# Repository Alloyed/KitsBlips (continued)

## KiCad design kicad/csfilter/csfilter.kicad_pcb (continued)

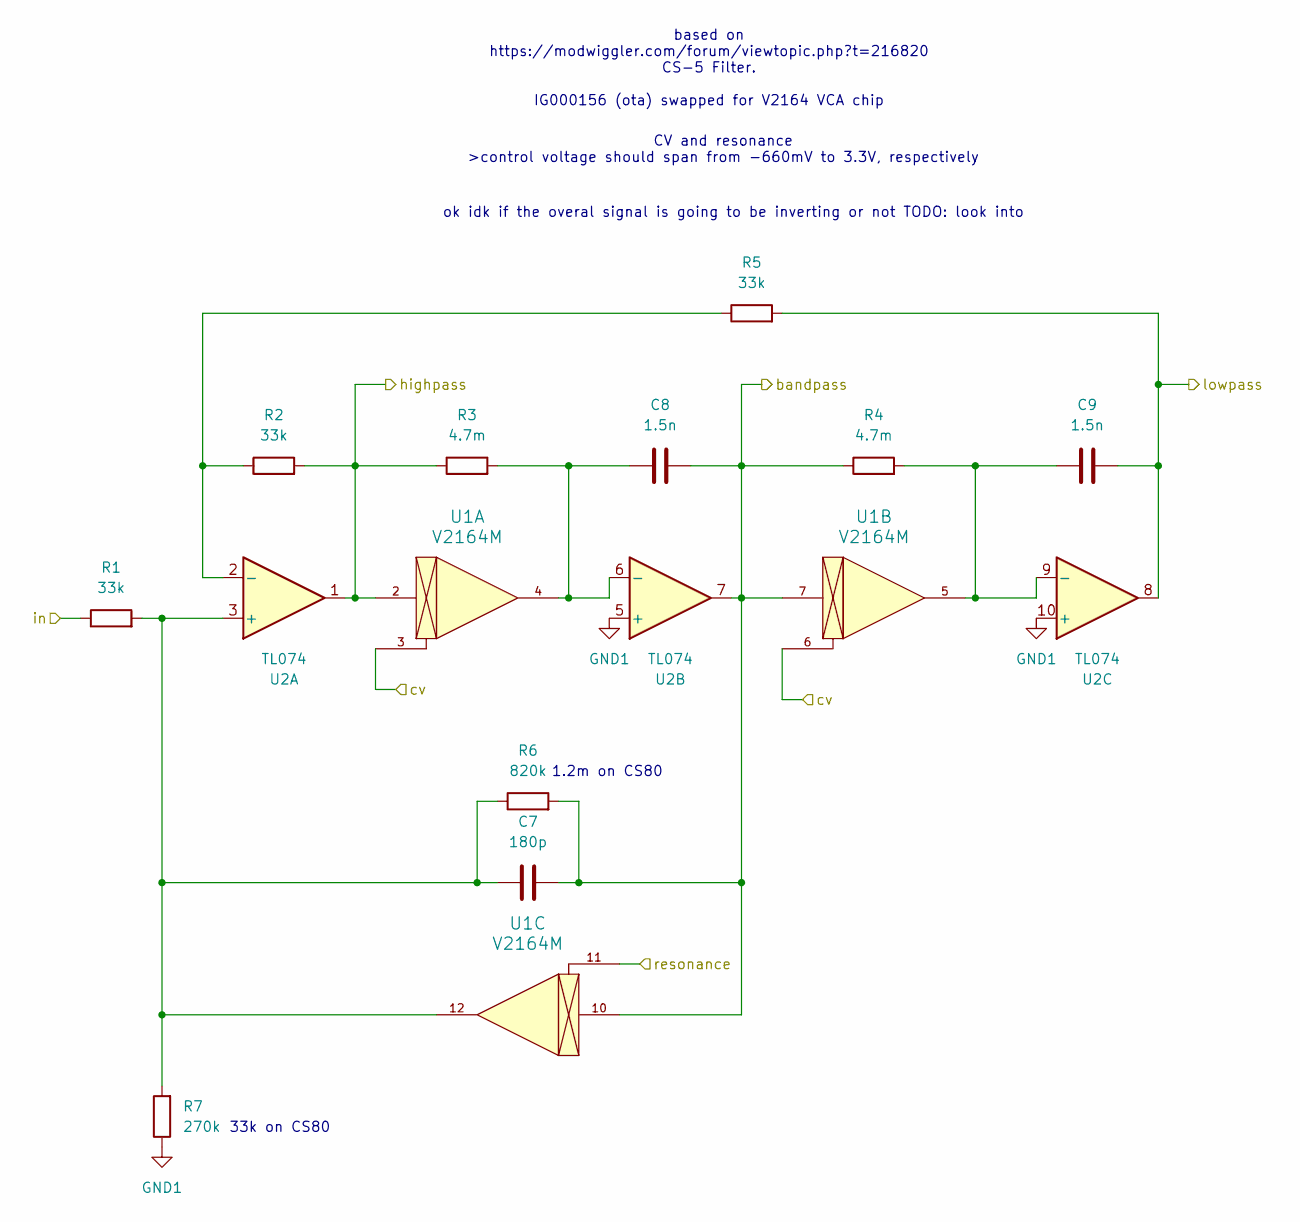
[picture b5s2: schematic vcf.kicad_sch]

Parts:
C7: 180p; C_Disc_D6.0mm_W2.5mm_P5.00mm
C8, C9: 1.5n; C_Disc_D6.0mm_W2.5mm_P5.00mm
R1, R2, R5: 33k; R_Axial_DIN0207_L6.3mm_D2.5mm_P7.62mm_Horizontal
R3, R4: 4.7m; R_Axial_DIN0207_L6.3mm_D2.5mm_P7.62mm_Horizontal
R6: 820k; R_Axial_DIN0207_L6.3mm_D2.5mm_P7.62mm_Horizontal
R7: 270k; R_Axial_DIN0207_L6.3mm_D2.5mm_P7.62mm_Horizontal
U1: V2164M; DIP-16_W7.62mm_Socket
U2: TL074; DIP-14_W7.62mm_Socket

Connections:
/input-cv1/A_OUT: U1.11; also elsewhere on the board
/input-cv/A_OUT: U1.3, U1.6; also elsewhere on the board
/vcf/bandpass: C7.2, C8.2, R4.1, R6.2, U1.7, U1.10, U2.7; also elsewhere on the board
/vcf/in: R1.1; also elsewhere on the board
/vcf/lowpass: C9.2, R5.2, U2.8; also elsewhere on the board
GND1: R7.1, U2.5 (+), U2.10 (+); also elsewhere on the board
unnamed: C7.1, R1.2, R6.1, R7.2, U1.12, U2.3 (+)
unnamed: C8.1, R3.2, U1.4, U2.6 (-)
unnamed: C9.1, R4.2, U1.5, U2.9 (-)

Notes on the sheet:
CV and resonance >control voltage should span from -660mV to 3.3V, respectively
33k on CS80
based on https://modwiggler.com/forum/viewtopic.php?t=216820 CS-5 Filter. IG000156 (ota) swapped for V2164 VCA chip
1.2m on CS80
ok idk if the overal signal is going to be inverting or not TODO: look into

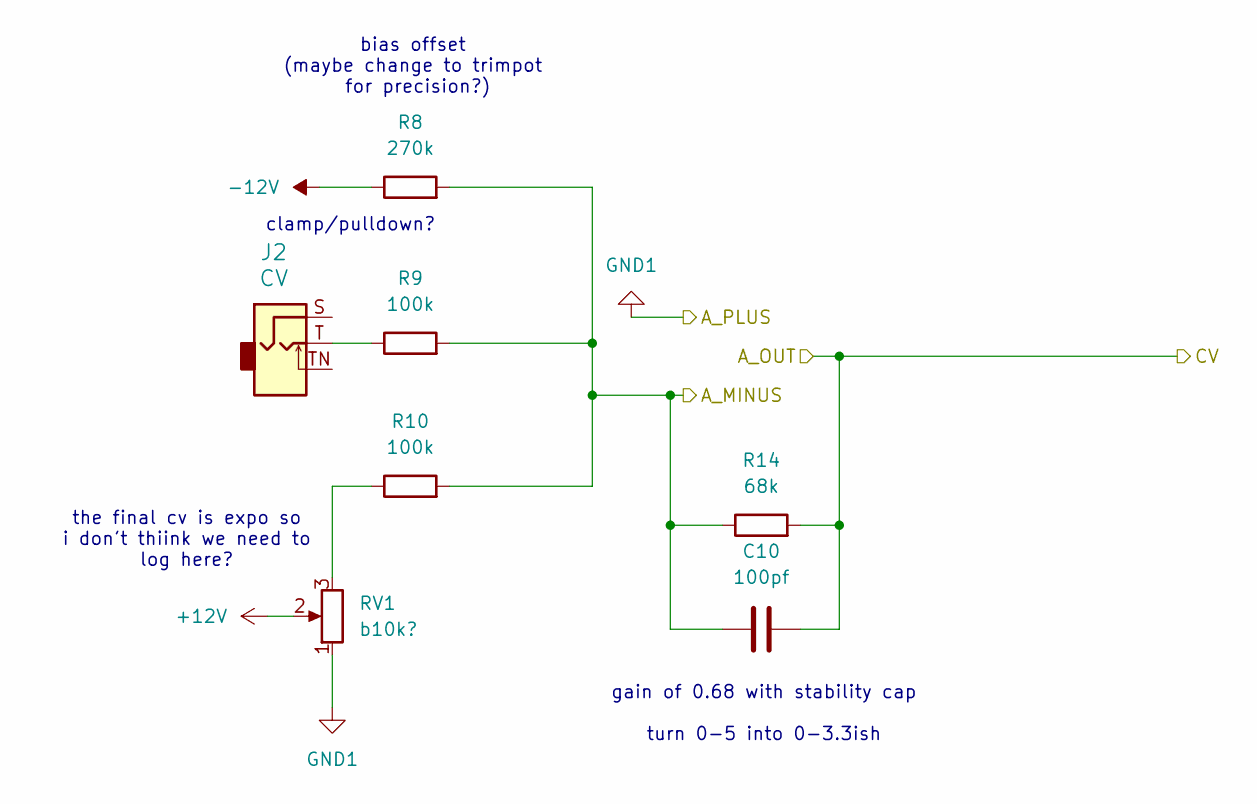
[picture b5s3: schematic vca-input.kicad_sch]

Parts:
C10: 100pf; C_Disc_D6.0mm_W2.5mm_P5.00mm
J2: CV; Jack_3.5mm_QingPu_WQP-PJ398SM_Vertical_CircularHoles; Part Number WQP-WQP518MA
R8: 270k; R_Axial_DIN0207_L6.3mm_D2.5mm_P7.62mm_Horizontal
R9, R10: 100k; R_Axial_DIN0207_L6.3mm_D2.5mm_P7.62mm_Horizontal
R14: 68k; R_Axial_DIN0207_L6.3mm_D2.5mm_P7.62mm_Horizontal
RV1: b10k?; Potentiometer_Alpha_RD901F-40-00D_Single_Vertical

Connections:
+12V: RV1.2; also elsewhere on the board
-12V: R8.1; also elsewhere on the board
/input-cv/A_MINUS: C10.1, R8.2, R9.2, R10.2, R14.1; also elsewhere on the board
/input-cv/A_OUT: C10.2, R14.2; also elsewhere on the board
GND1: RV1.1; also elsewhere on the board
unnamed: J2.T, R9.1
unnamed: R10.1, RV1.3

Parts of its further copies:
C11: 100pf; C_Disc_D6.0mm_W2.5mm_P5.00mm
J3: CV; Jack_3.5mm_QingPu_WQP-PJ398SM_Vertical_CircularHoles; Part Number WQP-WQP518MA
R11: 270k; R_Axial_DIN0207_L6.3mm_D2.5mm_P7.62mm_Horizontal
R12, R13: 100k; R_Axial_DIN0207_L6.3mm_D2.5mm_P7.62mm_Horizontal
R15: 68k; R_Axial_DIN0207_L6.3mm_D2.5mm_P7.62mm_Horizontal
RV2: b10k?; Potentiometer_Alpha_RD901F-40-00D_Single_Vertical

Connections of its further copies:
+12V: RV2.2; also elsewhere on the board
-12V: R11.1; also elsewhere on the board
/input-cv1/A_MINUS: C11.1, R11.2, R12.2, R13.2, R15.1; also elsewhere on the board
/input-cv1/A_OUT: C11.2, R15.2; also elsewhere on the board
GND1: RV2.1; also elsewhere on the board
unnamed: J3.T, R12.1
unnamed: R13.1, RV2.3

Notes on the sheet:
clamp/pulldown?
bias offset (maybe change to trimpot for precision?)
the final cv is expo so i don't thiink we need to log here?
gain of 0.68 with stability cap turn 0-5 into 0-3.3ish

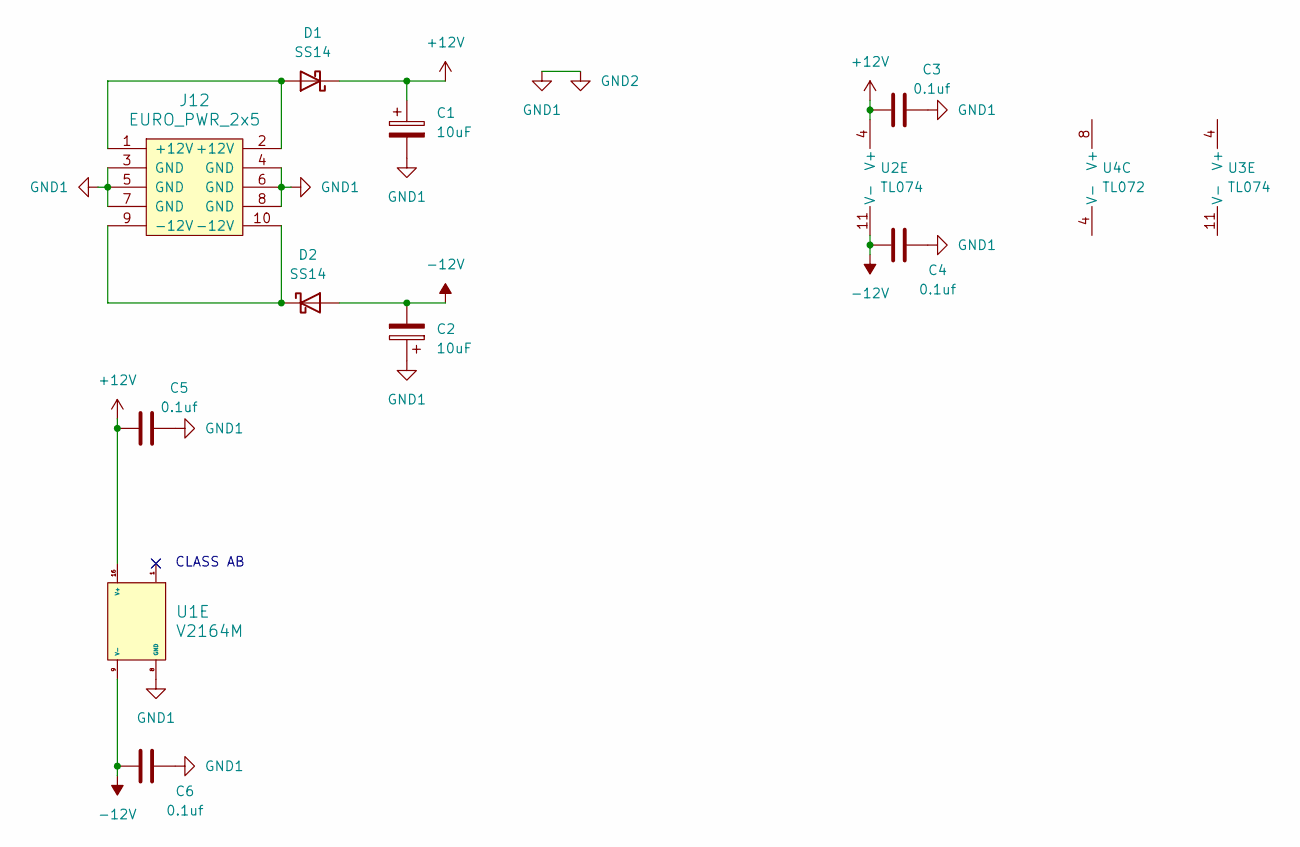
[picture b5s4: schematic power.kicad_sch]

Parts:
C1, C2: 10uF; CP_Radial_P2.5mm
C3, C4, C5, C6: 0.1uf; C_Disc_D6.0mm_W2.5mm_P5.00mm
D1, D2: SS14; D_SMA
J12: EURO_PWR_2x5; Pins_2x05_2.54mm_TH_Europower_shrouded
U1: V2164M; DIP-16_W7.62mm_Socket
U2, U3: TL074; DIP-14_W7.62mm_Socket
U4: TL072; DIP-8_W7.62mm_Socket

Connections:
+12V: C1.1, C3.1, C5.1, D1.1 (K), U1.16 (V+), U2.4 (V+); also elsewhere on the board
-12V: C2.2, C4.1, C6.1, D2.2 (A), U1.9 (V-), U2.11 (V-); also elsewhere on the board
GND1: C1.2, C2.1, C3.2, C4.2, C5.2, C6.2, J12.3 (GND), J12.4 (GND), J12.5 (GND), J12.6 (GND), J12.7 (GND), J12.8 (GND), U1.8 (GND); also elsewhere on the board
unnamed: D1.2 (A), J12.1 (+12V), J12.2 (+12V)
unnamed: D2.1 (K), J12.9 (-12V), J12.10 (-12V)

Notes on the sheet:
CLASS AB

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
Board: 2 copper layers, 44 parts (36 on the bottom side), 28 nets, no tracks yet.

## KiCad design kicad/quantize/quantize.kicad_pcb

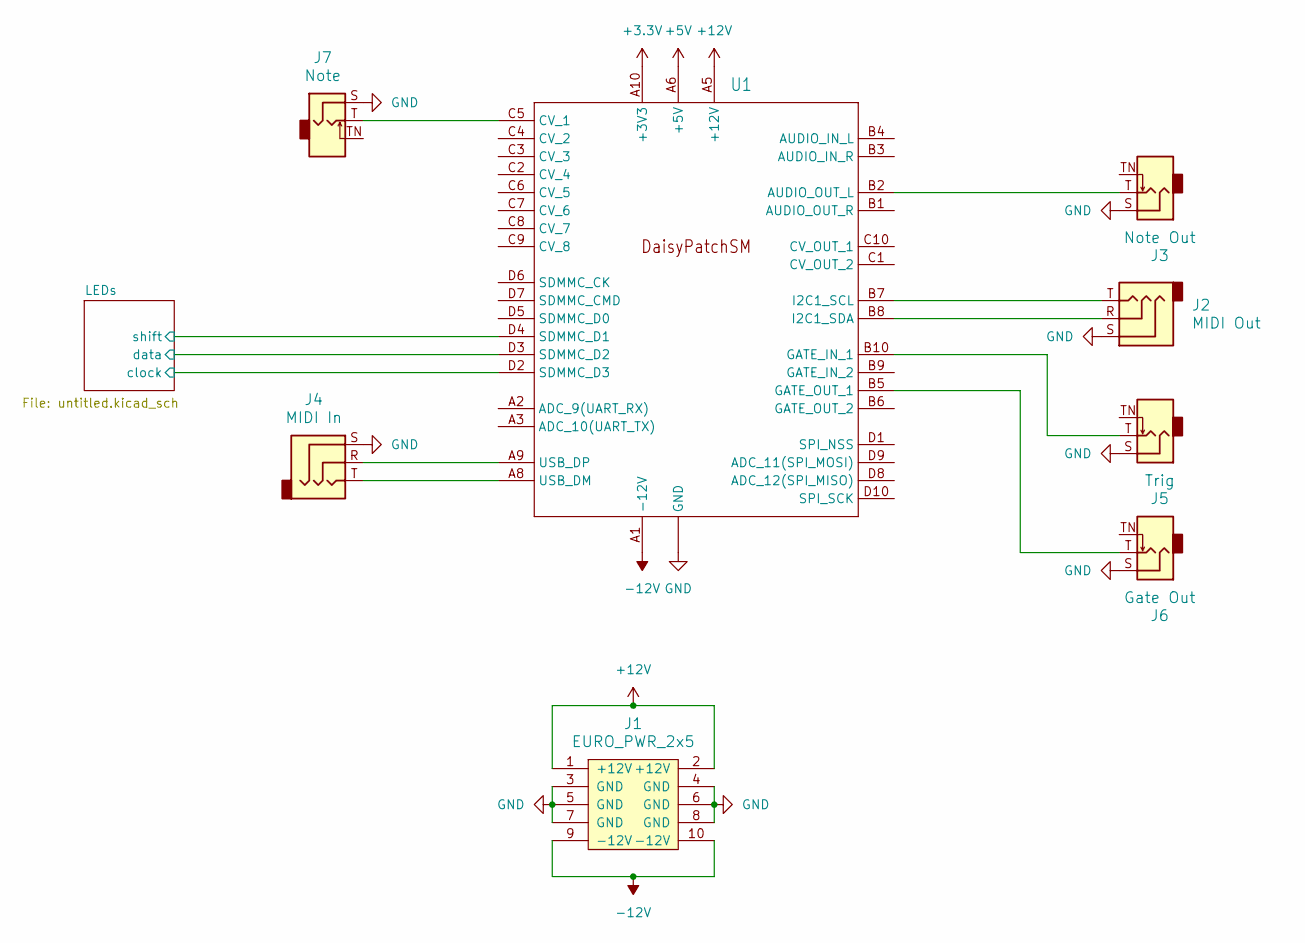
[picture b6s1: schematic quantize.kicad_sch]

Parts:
J1: EURO_PWR_2x5; Pins_2x05_2.54mm_TH_Europower_shrouded
J2: MIDI Out; Stereo_Thonk_PJ366ST; Part Number WQP-WQP419GR
J3: Note Out; Jack_3.5mm_QingPu_WQP-PJ398SM_Vertical_CircularHoles; Part Number WQP-WQP518MA
J4: MIDI In; Stereo_Thonk_PJ366ST; Part Number WQP-WQP419GR
J5: Trig; Jack_3.5mm_QingPu_WQP-PJ398SM_Vertical_CircularHoles; Part Number WQP-WQP518MA
J6: Gate Out; Jack_3.5mm_QingPu_WQP-PJ398SM_Vertical_CircularHoles; Part Number WQP-WQP518MA
J7: Note; Jack_3.5mm_QingPu_WQP-PJ398SM_Vertical_CircularHoles; Part Number WQP-WQP518MA
U1: ES_DAISY_PATCH_SM_REV1

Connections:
+3.3V: U1.A10 (+3V3); also elsewhere on the board
+5V: U1.A6 (+5V); also elsewhere on the board
+12V: J1.1 (+12V), J1.2 (+12V), U1.A5 (+12V)
-12V: J1.9 (-12V), J1.10 (-12V), U1.A1 (-12V)
/LEDs/clock: U1.D2 (SDMMC_D3); also elsewhere on the board
/LEDs/data: U1.D3 (SDMMC_D2); also elsewhere on the board
/LEDs/shift: U1.D4 (SDMMC_D1); also elsewhere on the board
GND: J1.3 (GND), J1.4 (GND), J1.5 (GND), J1.6 (GND), J1.7 (GND), J1.8 (GND), J2.S, J3.S, J4.S, J5.S, J6.S, J7.S, U1.A4 (GND), U1.A7 (GND); also elsewhere on the board
unnamed: J3.T, U1.B2 (AUDIO_OUT_L)
unnamed: J7.T, U1.C5 (CV_1)
unnamed: J5.T, U1.B10 (GATE_IN_1)
unnamed: J6.T, U1.B5 (GATE_OUT_1)
unnamed: J2.T, U1.B7 (I2C1_SCL)
unnamed: J2.R, U1.B8 (I2C1_SDA)
unnamed: J4.T, U1.A8 (USB_DM)
unnamed: J4.R, U1.A9 (USB_DP)

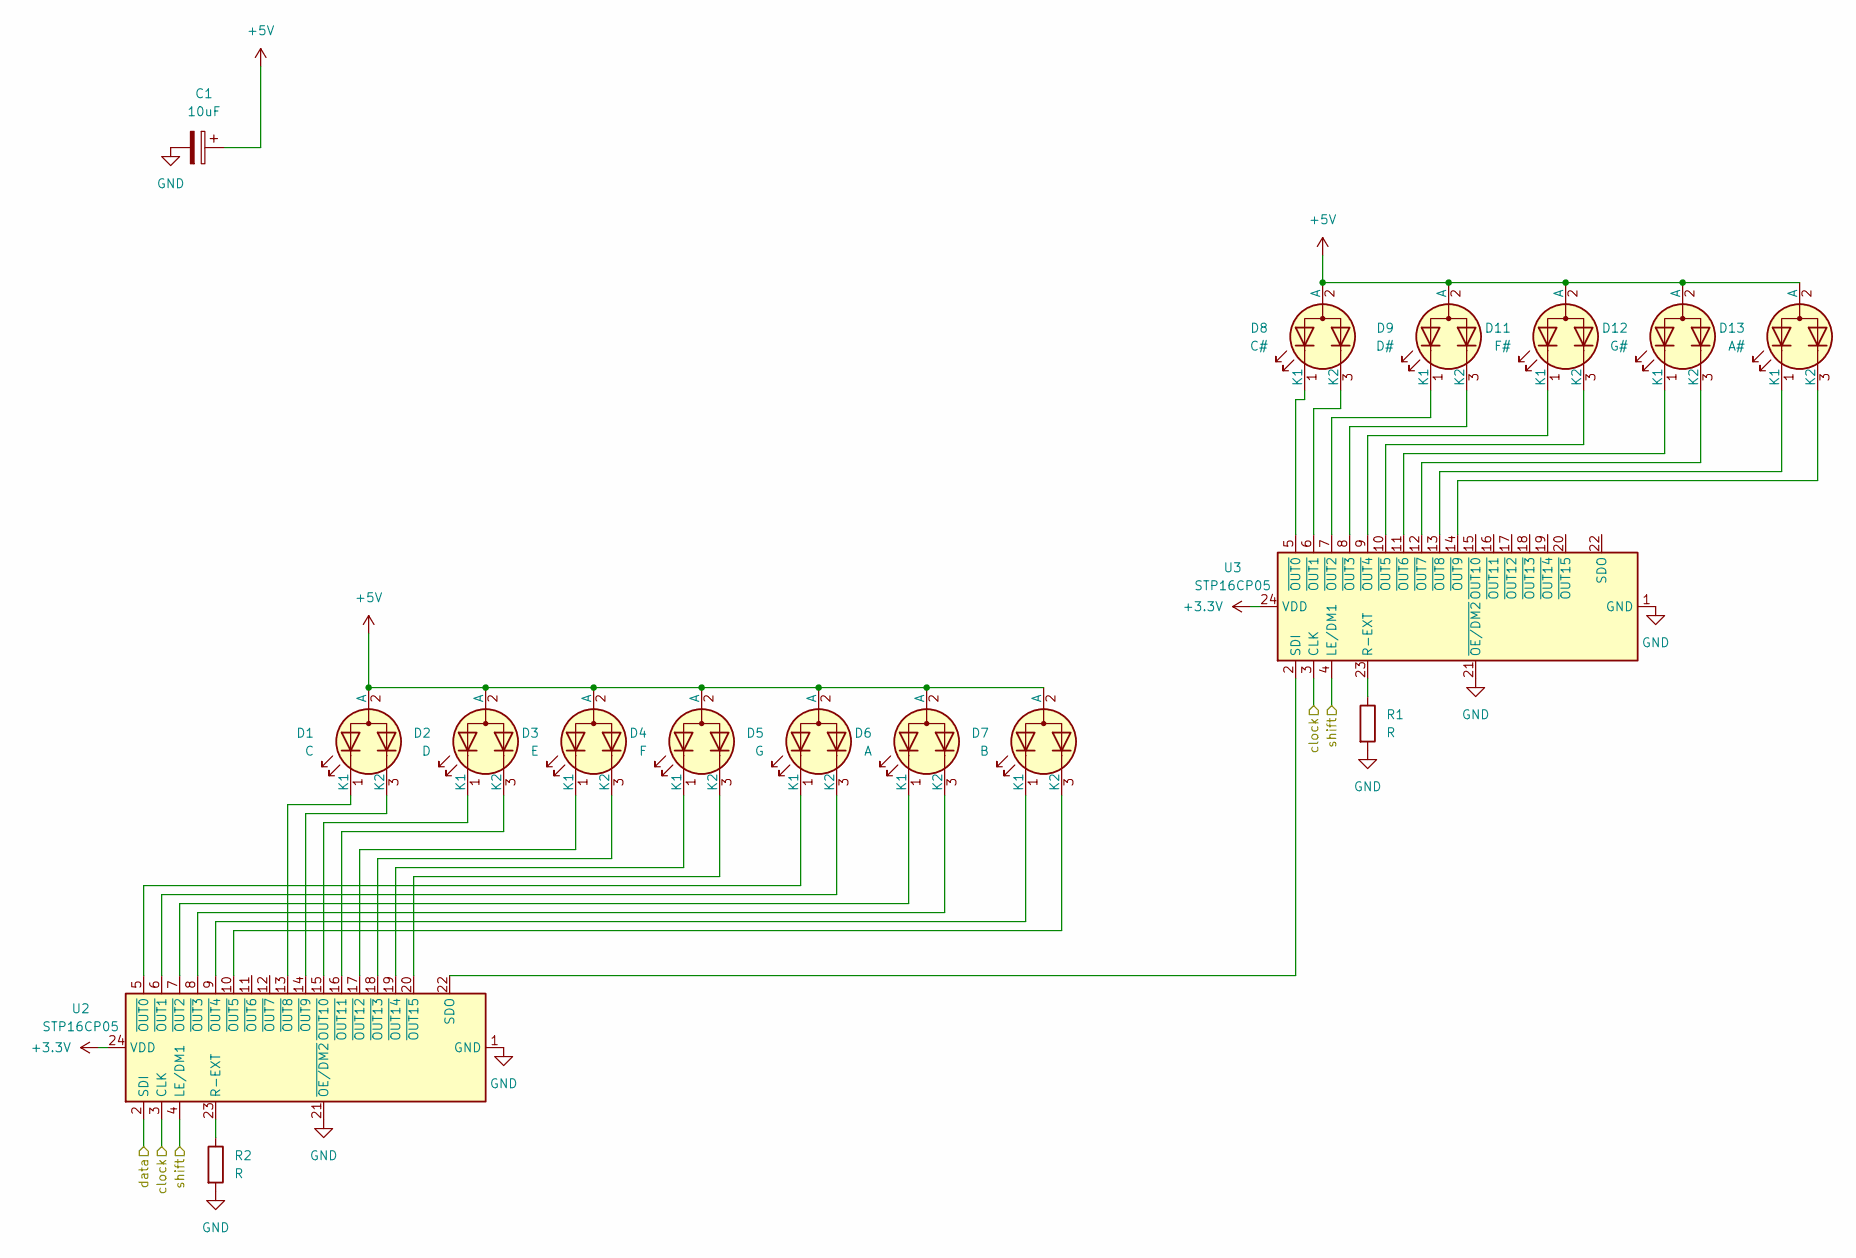
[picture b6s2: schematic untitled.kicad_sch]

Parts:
C1: 10uF; CP_Radial_P2.5mm
D1: C; LED_D3.0mm-3
D2: D; LED_D3.0mm-3
D3: E; LED_D3.0mm-3
D4: F; LED_D3.0mm-3
D5: G; LED_D3.0mm-3
D6: A; LED_D3.0mm-3
D7: B; LED_D3.0mm-3
D8: C#; LED_D3.0mm-3
D9: D#; LED_D3.0mm-3
D11: F#; LED_D3.0mm-3
D12: G#; LED_D3.0mm-3
D13: A#; LED_D3.0mm-3
R1, R2: R; R_Axial_DIN0207_L6.3mm_D2.5mm_P7.62mm_Horizontal
U2, U3: STP16CP05; SOIC-24W_7.5x15.4mm_P1.27mm

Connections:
+3.3V: U2.24 (VDD), U3.24 (VDD); also elsewhere on the board
+5V: C1.1, D1.2 (A), D2.2 (A), D3.2 (A), D4.2 (A), D5.2 (A), D6.2 (A), D7.2 (A), D8.2 (A), D9.2 (A), D11.2 (A), D12.2 (A), D13.2 (A); also elsewhere on the board
/LEDs/clock: U2.3 (CLK), U3.3 (CLK); also elsewhere on the board
/LEDs/data: U2.2 (SDI); also elsewhere on the board
/LEDs/shift: U2.4 (LE/DM1), U3.4 (LE/DM1); also elsewhere on the board
GND: C1.2, R1.2, R2.2, U2.1 (GND), U2.21 (~OE/DM2), U3.1 (GND), U3.21 (~OE/DM2); also elsewhere on the board
unnamed: D1.1 (K1), U2.13 (~OUT8)
unnamed: D1.3 (K2), U2.14 (~OUT9)
unnamed: D2.1 (K1), U2.15 (~OUT10)
unnamed: D2.3 (K2), U2.16 (~OUT11)
unnamed: D3.1 (K1), U2.17 (~OUT12)
unnamed: D3.3 (K2), U2.18 (~OUT13)
unnamed: D4.1 (K1), U2.19 (~OUT14)
unnamed: D4.3 (K2), U2.20 (~OUT15)
unnamed: D5.1 (K1), U2.5 (~OUT0)
unnamed: D5.3 (K2), U2.6 (~OUT1)
unnamed: D6.1 (K1), U2.7 (~OUT2)
unnamed: D6.3 (K2), U2.8 (~OUT3)
unnamed: D7.1 (K1), U2.9 (~OUT4)
unnamed: D7.3 (K2), U2.10 (~OUT5)
unnamed: D8.1 (K1), U3.5 (~OUT0)
unnamed: D8.3 (K2), U3.6 (~OUT1)
unnamed: D9.1 (K1), U3.7 (~OUT2)
unnamed: D9.3 (K2), U3.8 (~OUT3)
unnamed: D11.1 (K1), U3.9 (~OUT4)
unnamed: D11.3 (K2), U3.10 (~OUT5)
unnamed: D12.1 (K1), U3.11 (~OUT6)
unnamed: D12.3 (K2), U3.12 (~OUT7)
unnamed: D13.1 (K1), U3.13 (~OUT8)
unnamed: D13.3 (K2), U3.14 (~OUT9)
unnamed: R2.1, U2.23 (R-EXT)
unnamed: U2.22 (SDO), U3.2 (SDI)
unnamed: R1.1, U3.23 (R-EXT)

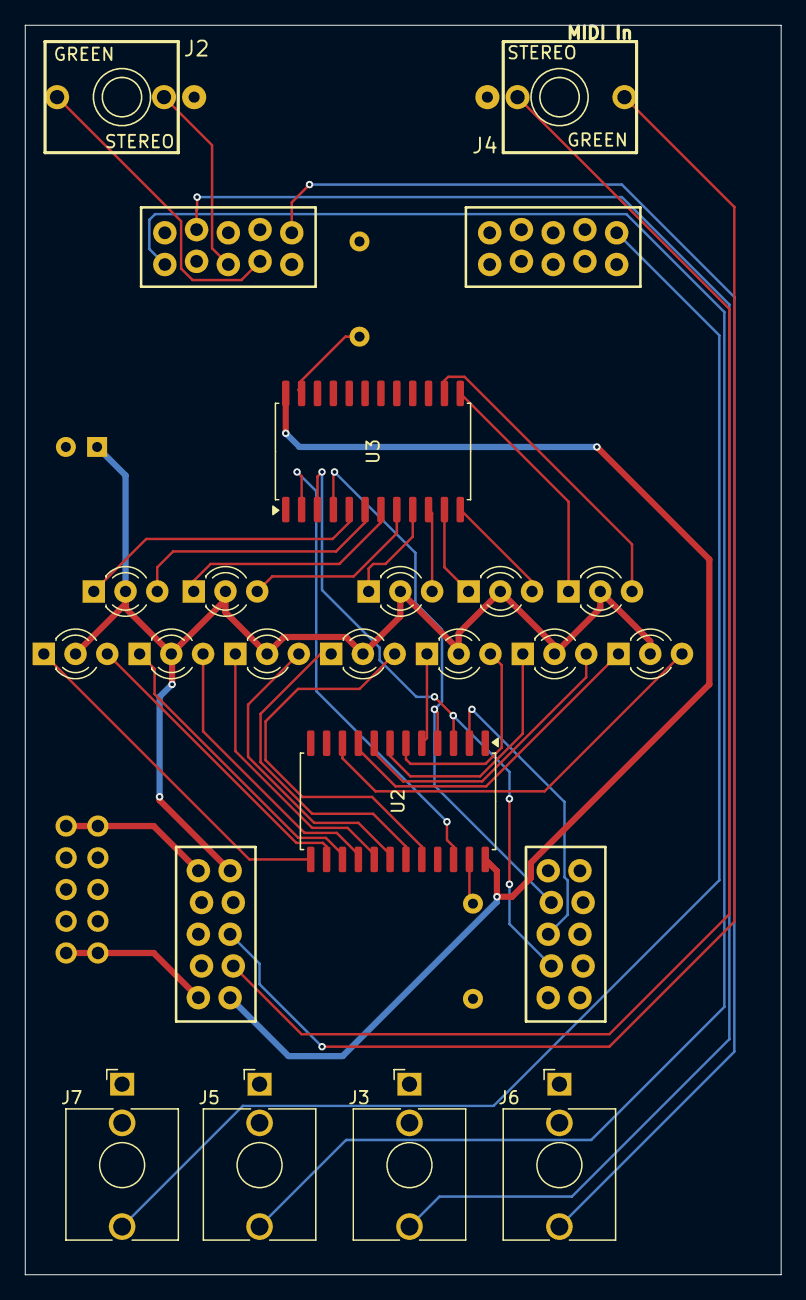
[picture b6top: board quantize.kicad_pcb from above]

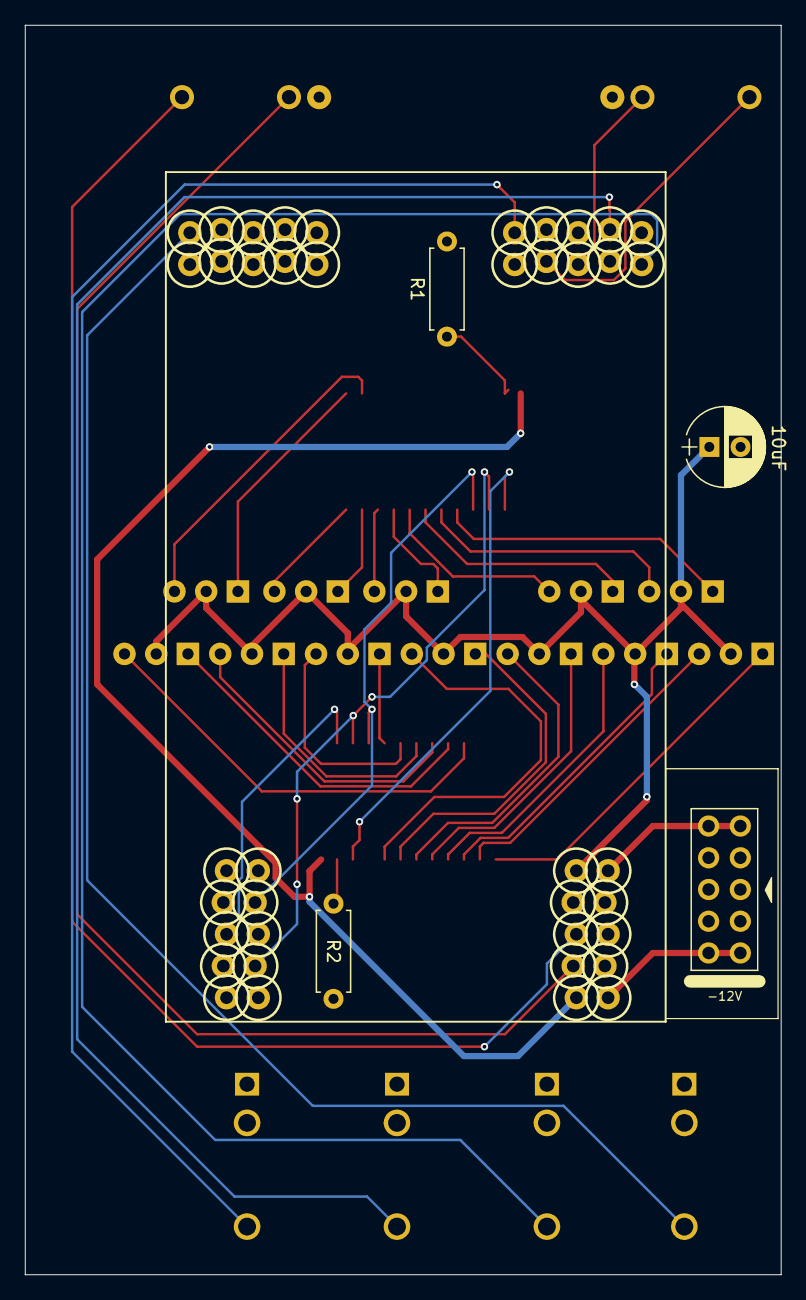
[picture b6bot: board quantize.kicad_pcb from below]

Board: 2 copper layers, 60.5 x 100.0 mm, 25 parts (5 on the bottom side), 43 nets.

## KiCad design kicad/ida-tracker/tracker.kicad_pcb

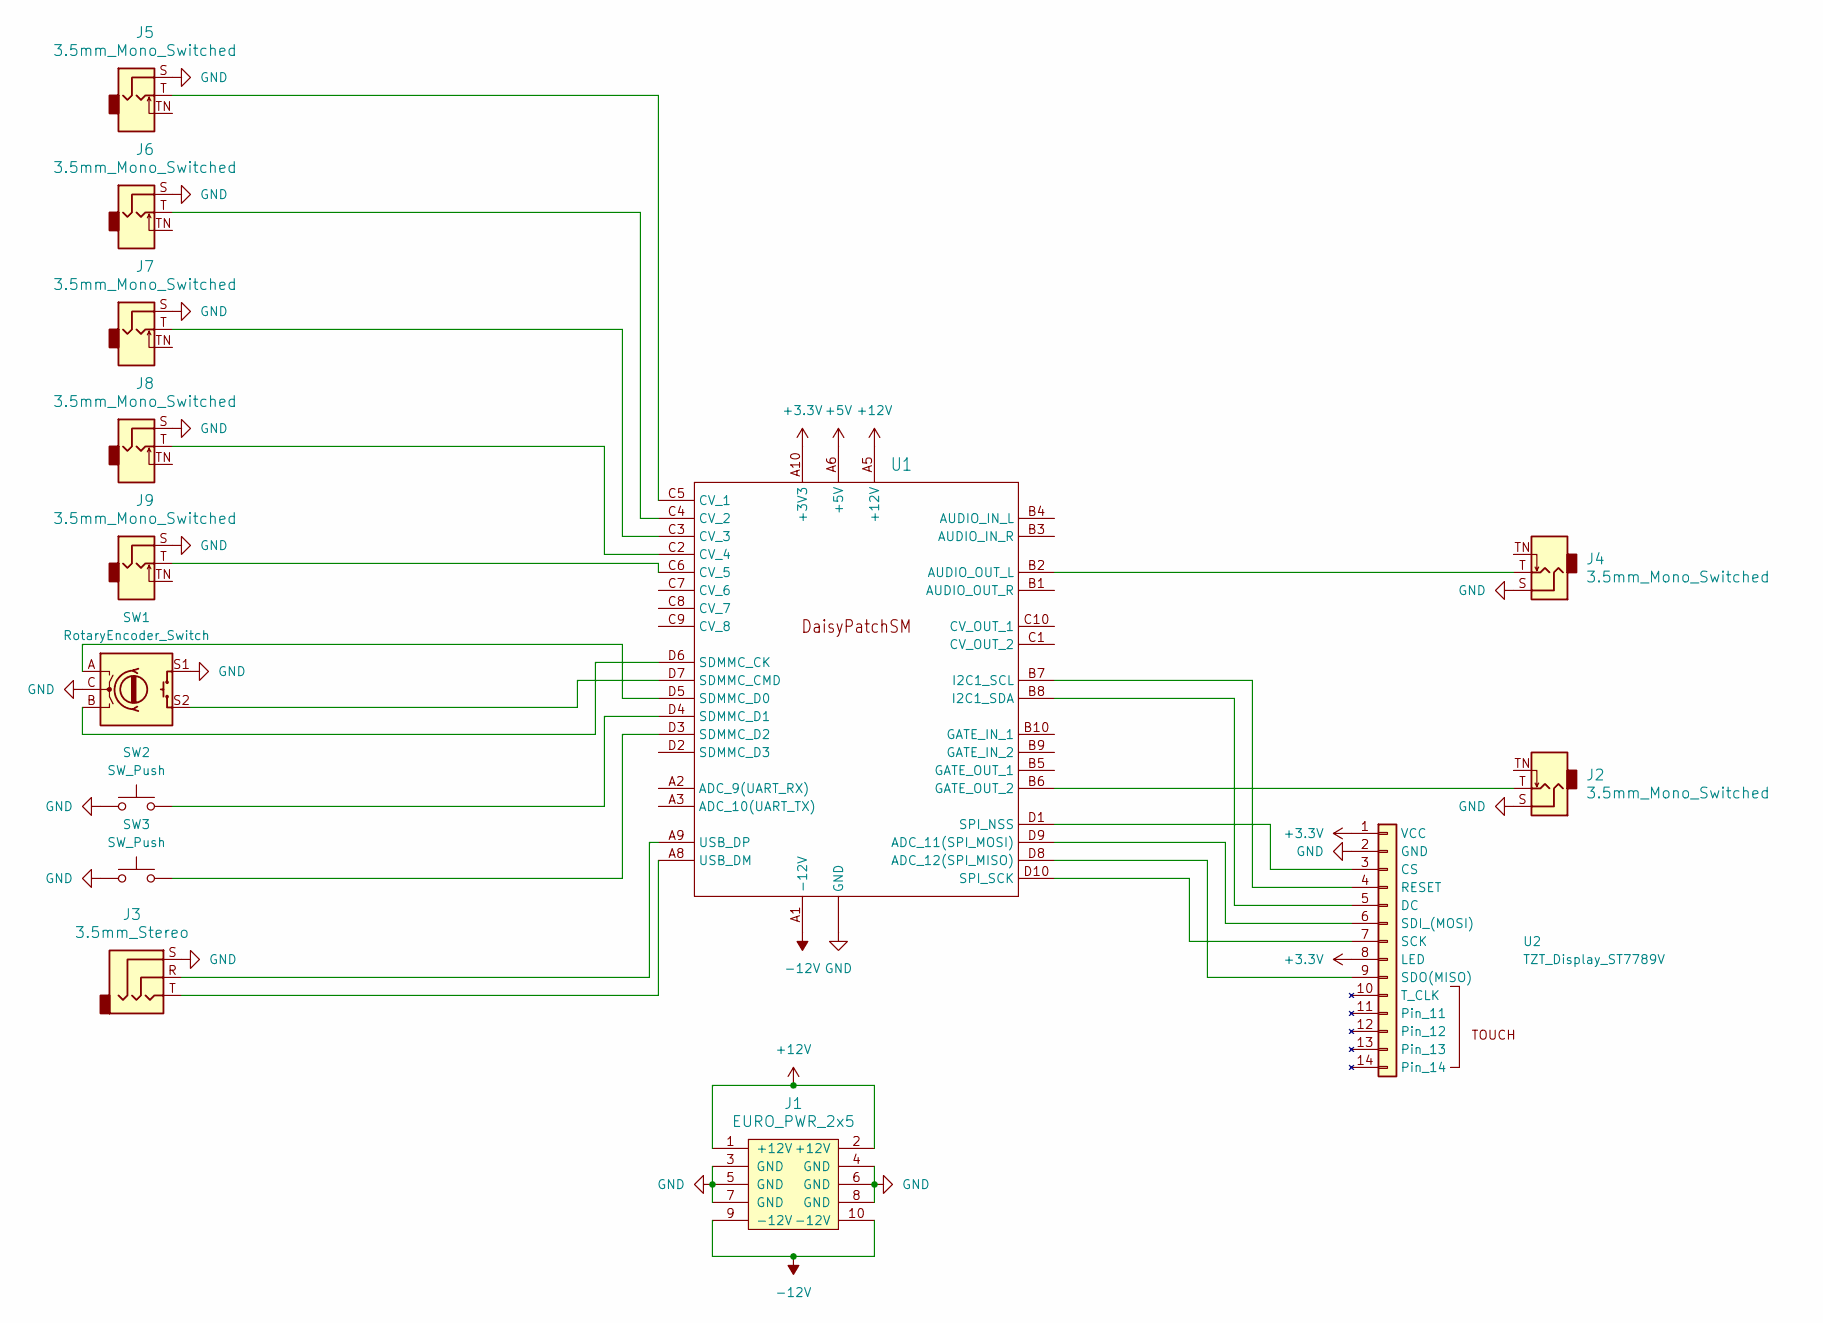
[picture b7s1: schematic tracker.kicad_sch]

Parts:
J1: EURO_PWR_2x5; Pins_2x05_2.54mm_TH_Europower_shrouded
J2, J4, J5, J6, J7, J8, J9: 3.5mm_Mono_Switched; Jack_3.5mm_QingPu_WQP-PJ398SM_Vertical_CircularHoles; Part Number WQP-WQP518MA
J3: 3.5mm_Stereo; Stereo_Thonk_PJ366ST; Part Number WQP-WQP419GR
SW1: RotaryEncoder_Switch; RotaryEncoder_Bourns_Vertical_PEC12R-3x17F-Sxxxx
SW2, SW3: SW_Push; SW_PUSH_6mm_H13mm
U1: ES_DAISY_PATCH_SM_REV1
U2: TZT_Display_ST7789V

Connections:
+3.3V: U1.A10 (+3V3), U2.1 (VCC), U2.8 (LED)
+5V: U1.A6 (+5V)
+12V: J1.1 (+12V), J1.2 (+12V), U1.A5 (+12V)
-12V: J1.9 (-12V), J1.10 (-12V), U1.A1 (-12V)
GND: J1.3 (GND), J1.4 (GND), J1.5 (GND), J1.6 (GND), J1.7 (GND), J1.8 (GND), J2.S, J3.S, J4.S, J5.S, J6.S, J7.S, J8.S, J9.S, SW1.C, SW1.S1, SW2.1, SW3.1, U1.A4 (GND), U1.A7 (GND), U2.2 (GND)
unnamed: U1.D9 (ADC_11(SPI_MOSI)), U2.6 (SDI_(MOSI))
unnamed: U1.D8 (ADC_12(SPI_MISO)), U2.9 (SDO(MISO))
unnamed: J4.T, U1.B2 (AUDIO_OUT_L)
unnamed: J5.T, U1.C5 (CV_1)
unnamed: J6.T, U1.C4 (CV_2)
unnamed: J7.T, U1.C3 (CV_3)
unnamed: J8.T, U1.C2 (CV_4)
unnamed: J9.T, U1.C6 (CV_5)
unnamed: J2.T, U1.B6 (GATE_OUT_2)
unnamed: U1.B7 (I2C1_SCL), U2.4 (RESET)
unnamed: U1.B8 (I2C1_SDA), U2.5 (DC)
unnamed: SW1.B, U1.D6 (SDMMC_CK)
unnamed: SW1.S2, U1.D7 (SDMMC_CMD)
unnamed: SW1.A, U1.D5 (SDMMC_D0)
unnamed: SW2.2, U1.D4 (SDMMC_D1)
unnamed: SW3.2, U1.D3 (SDMMC_D2)
unnamed: U1.D1 (SPI_NSS), U2.3 (CS)
unnamed: U1.D10 (SPI_SCK), U2.7 (SCK)
unnamed: J3.T, U1.A8 (USB_DM)
unnamed: J3.R, U1.A9 (USB_DP)

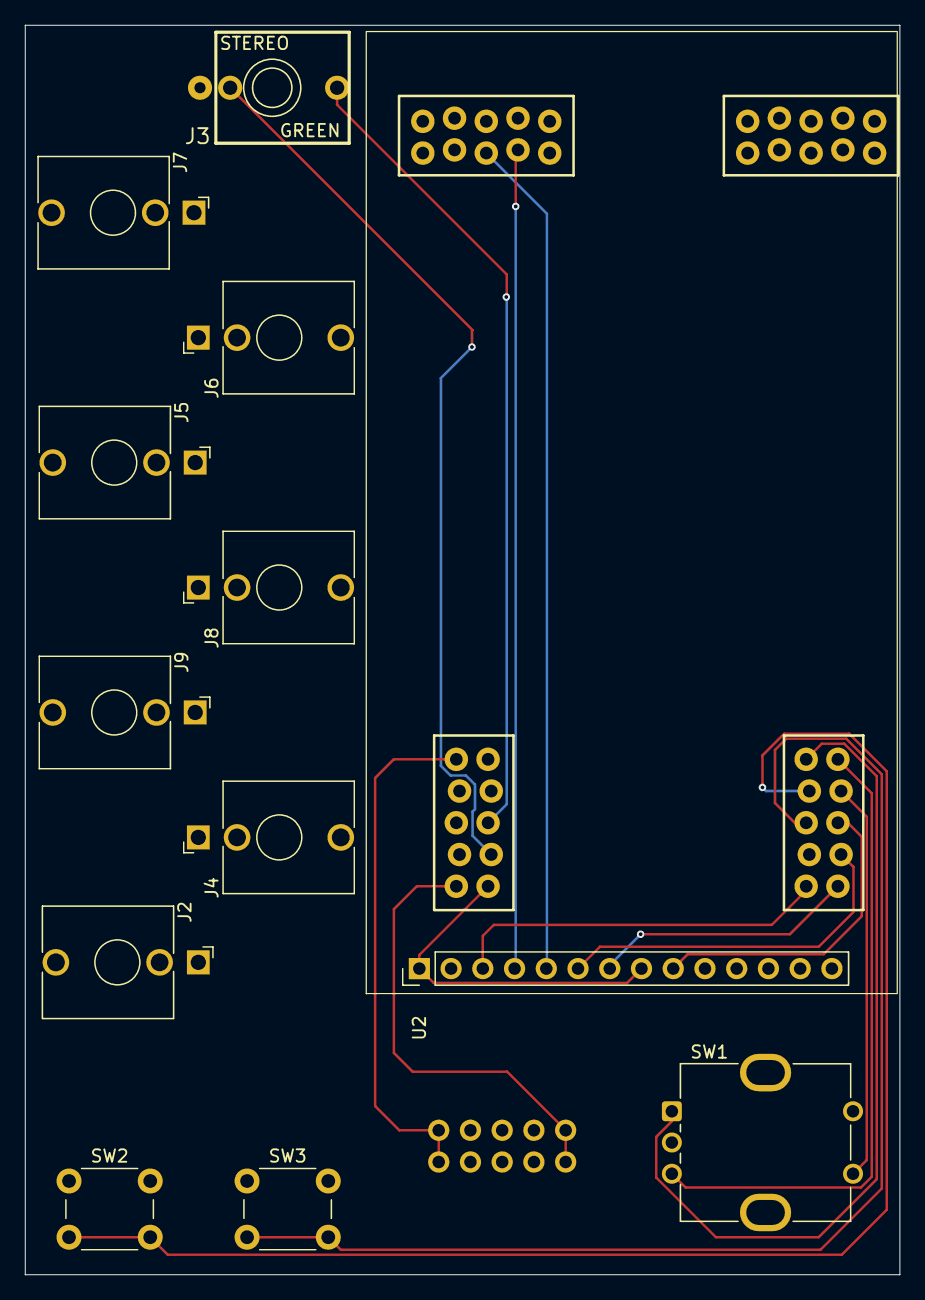
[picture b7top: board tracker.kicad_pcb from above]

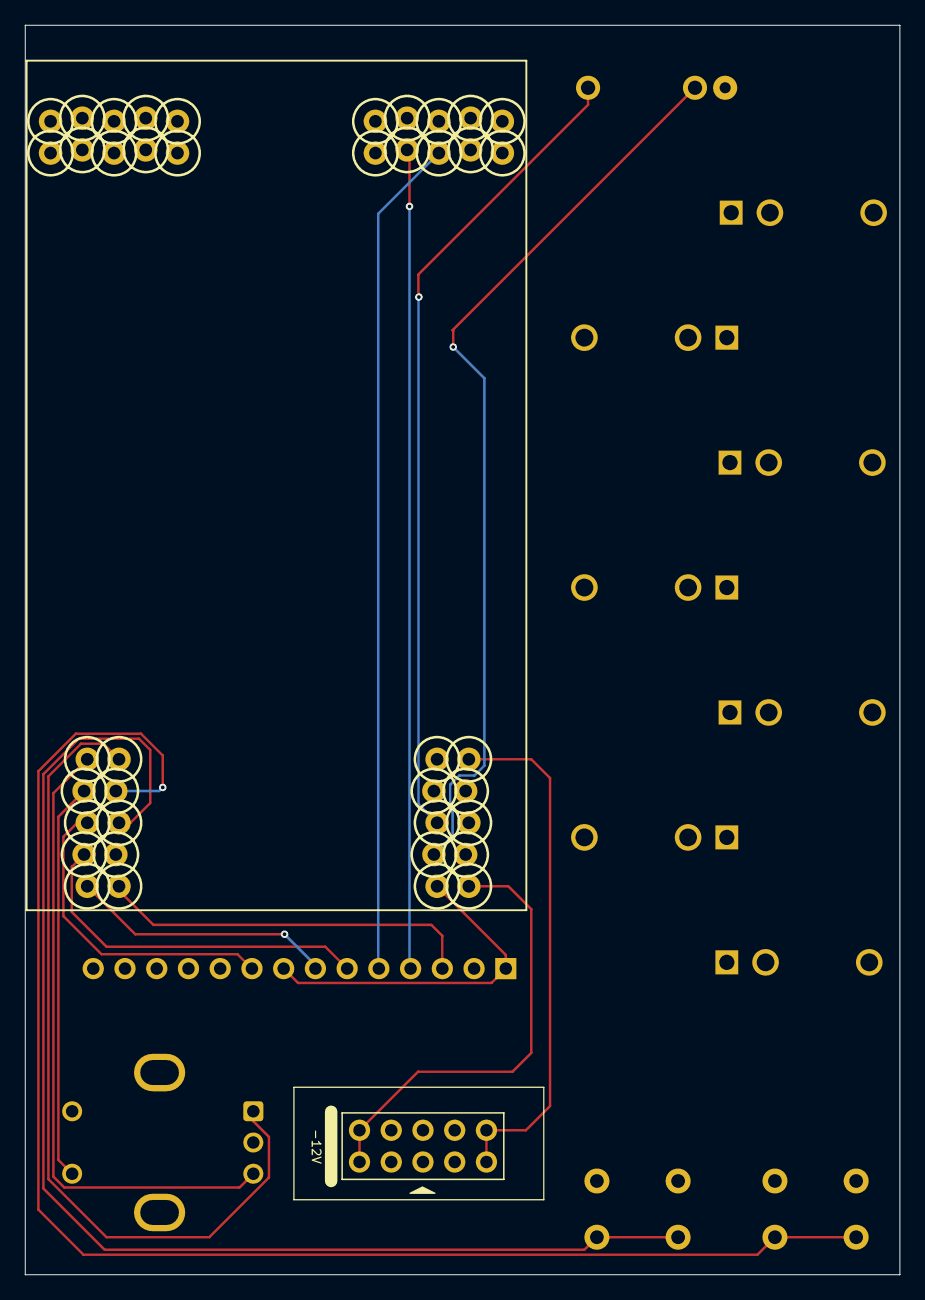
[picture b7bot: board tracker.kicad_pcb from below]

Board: 2 copper layers, 70.0 x 100.0 mm, 14 parts (2 on the bottom side), 24 nets.
